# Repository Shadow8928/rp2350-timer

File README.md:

# XIAO-RP2350-Timer
I made this project in order to track the time i spend when doing certain tasks but i didn't want to use my phone in order to avoid distraction as well as when i study or work during the school day when i don't have my phone on me. originally the plan was to use an rp2040 chip with components but it proved too complicated for me to use and required equipment i didn't have. I decided on a xiao rp2350 as it already had lipo battery use prebuilt and was small to allow for the small form factor i was aiming for. 
## Parts List

| Item | Price | Link|
|---|---:|---|
| XIAO RP2350 | $1.09 | [AliExpress](https://www.aliexpress.us/item/3256812349541468.html) |
| Diodes | $2.49 | [AliExpress](https://www.aliexpress.us/item/3256807166031523.html) |
| LiPo battery | $1.09 | [AliExpress](https://www.aliexpress.us/item/3256803193874231.html) |
| Cherry switches | $0.33 | AliExpress — 3 for $0.99 |
| Buzzers | $0.33 | AliExpress — 3 for $0.99 |
| 0.91-inch OLED screen | $0.33 | AliExpress — 3 for $0.99 |
| LED diodes | $3.41 | [AliExpress](https://www.aliexpress.us/item/3256810339576661.html) |
| PCB | $11.01 | [JLCPCB](https://jlcpcb.com/) |
| Liquid flux | $4.85 | [AliExpress](https://www.aliexpress.us/item/3256804676815166.html) |
| **Total** | **$24.93** | |

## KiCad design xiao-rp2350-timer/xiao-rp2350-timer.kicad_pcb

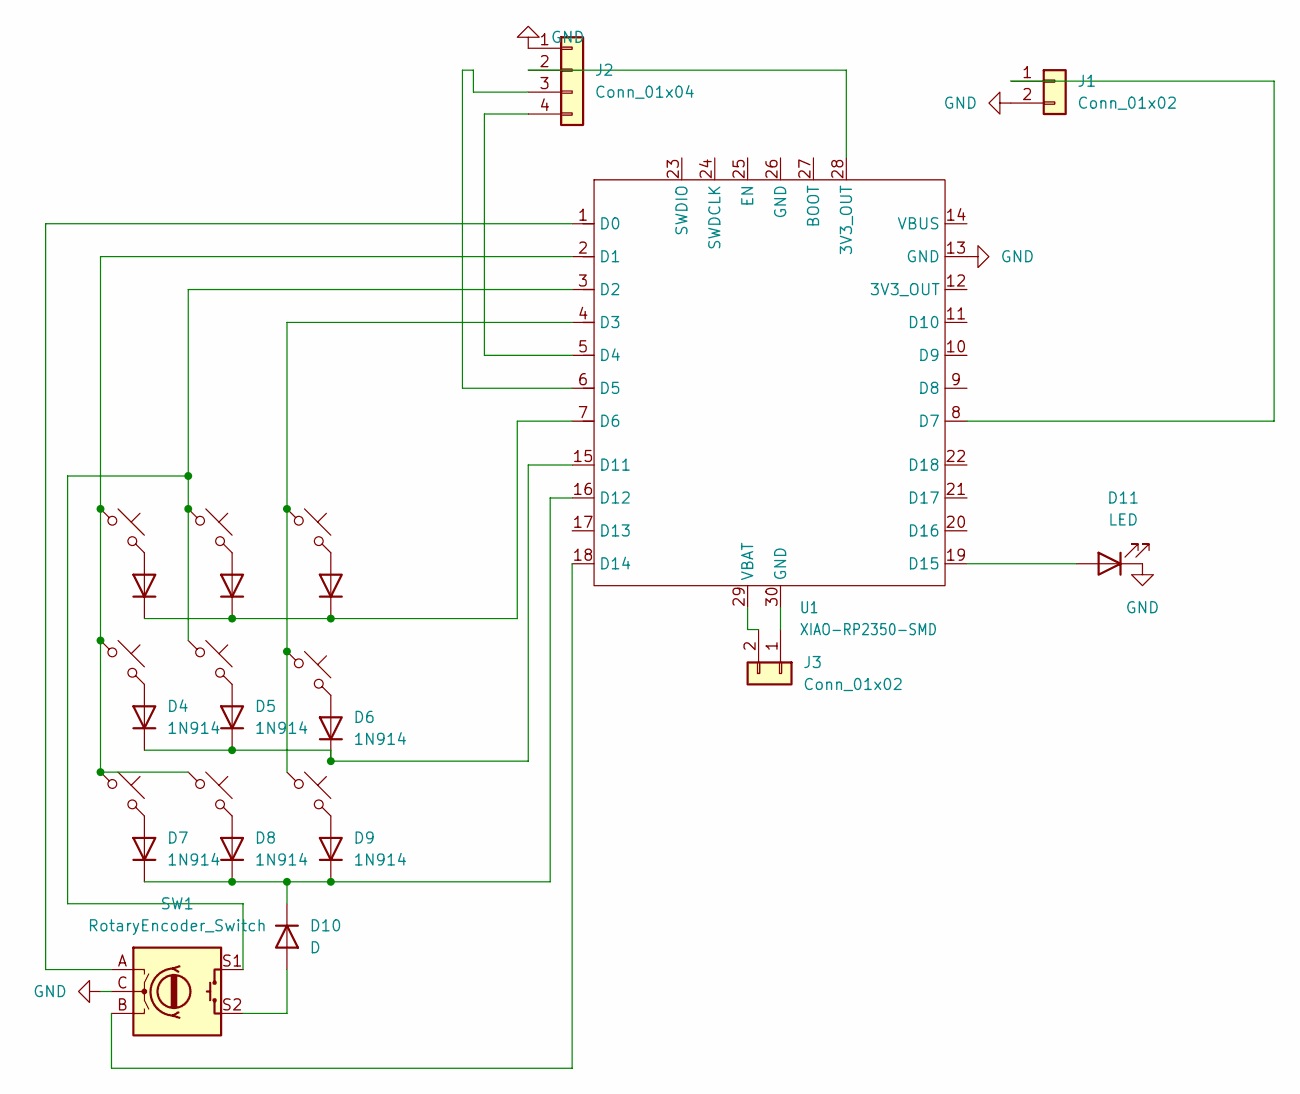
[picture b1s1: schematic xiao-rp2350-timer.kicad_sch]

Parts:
D1, D2, D3, D4, D5, D6, D7, D8, D9: 1N914; D_SOD-323_HandSoldering
D10: D; D_SOD-323_HandSoldering
D11: LED; LED_0805_2012Metric
J1, J3: Conn_01x02; JWT_A3963_1x02_P3.96mm_Vertical
J2: Conn_01x04; SSD1306-0.91-OLED-4pin-128x32
SW1: RotaryEncoder_Switch; RotaryEncoder_Alps_EC11E-Switch_Vertical_H20mm_MountingHoles
SW2, SW3, SW4, SW5, SW6, SW7, SW8, SW9, SW10: SW_Push_45deg; MX-Solderable-1U
U1: XIAO-RP2350-SMD

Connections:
GND: D11.1 (K), J1.2, J2.1, SW1.C, U1.13 (GND)
unnamed: D1.2 (A), SW2.2
unnamed: D1.1 (K), D2.1 (K), D3.1 (K), U1.7 (D6)
unnamed: D2.2 (A), SW3.2
unnamed: D3.2 (A), SW4.2
unnamed: D4.2 (A), SW5.2
unnamed: D4.1 (K), D5.1 (K), D6.1 (K), U1.15 (D11)
unnamed: D5.2 (A), SW6.2
unnamed: D6.2 (A), SW7.2
unnamed: D7.2 (A), SW8.2
unnamed: D8.2 (A), SW9.2
unnamed: D9.2 (A), SW10.2
unnamed: D10.2 (A), SW1.S2
unnamed: D7.1 (K), D8.1 (K), D9.1 (K), D10.1 (K), U1.16 (D12)
unnamed: D11.2 (A), U1.19 (D15)
unnamed: J1.1, U1.8 (D7)
unnamed: J2.2, U1.28 (3V3_OUT)
unnamed: J2.3, U1.6 (D5)
unnamed: J2.4, U1.5 (D4)
unnamed: J3.1, U1.30 (GND)
unnamed: J3.2, U1.29 (VBAT)
unnamed: SW1.A, U1.1 (D0)
unnamed: SW2.1, SW5.1, SW8.1, SW9.1, U1.2 (D1)
unnamed: SW1.S1, SW3.1, SW6.1, U1.3 (D2)
unnamed: SW4.1, SW7.1, SW10.1, U1.4 (D3)
unnamed: SW1.B, U1.18 (D14)

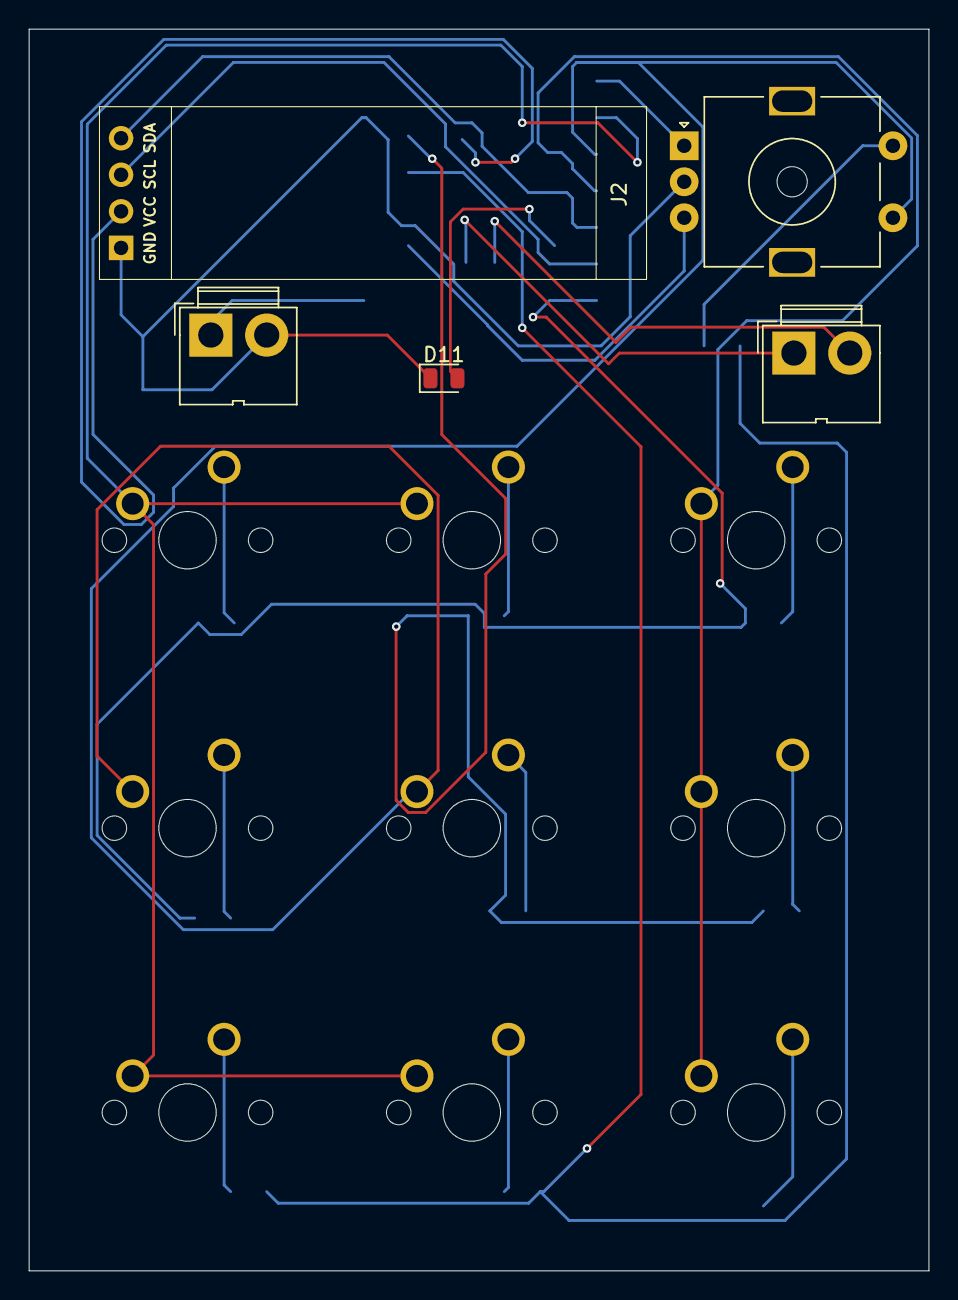
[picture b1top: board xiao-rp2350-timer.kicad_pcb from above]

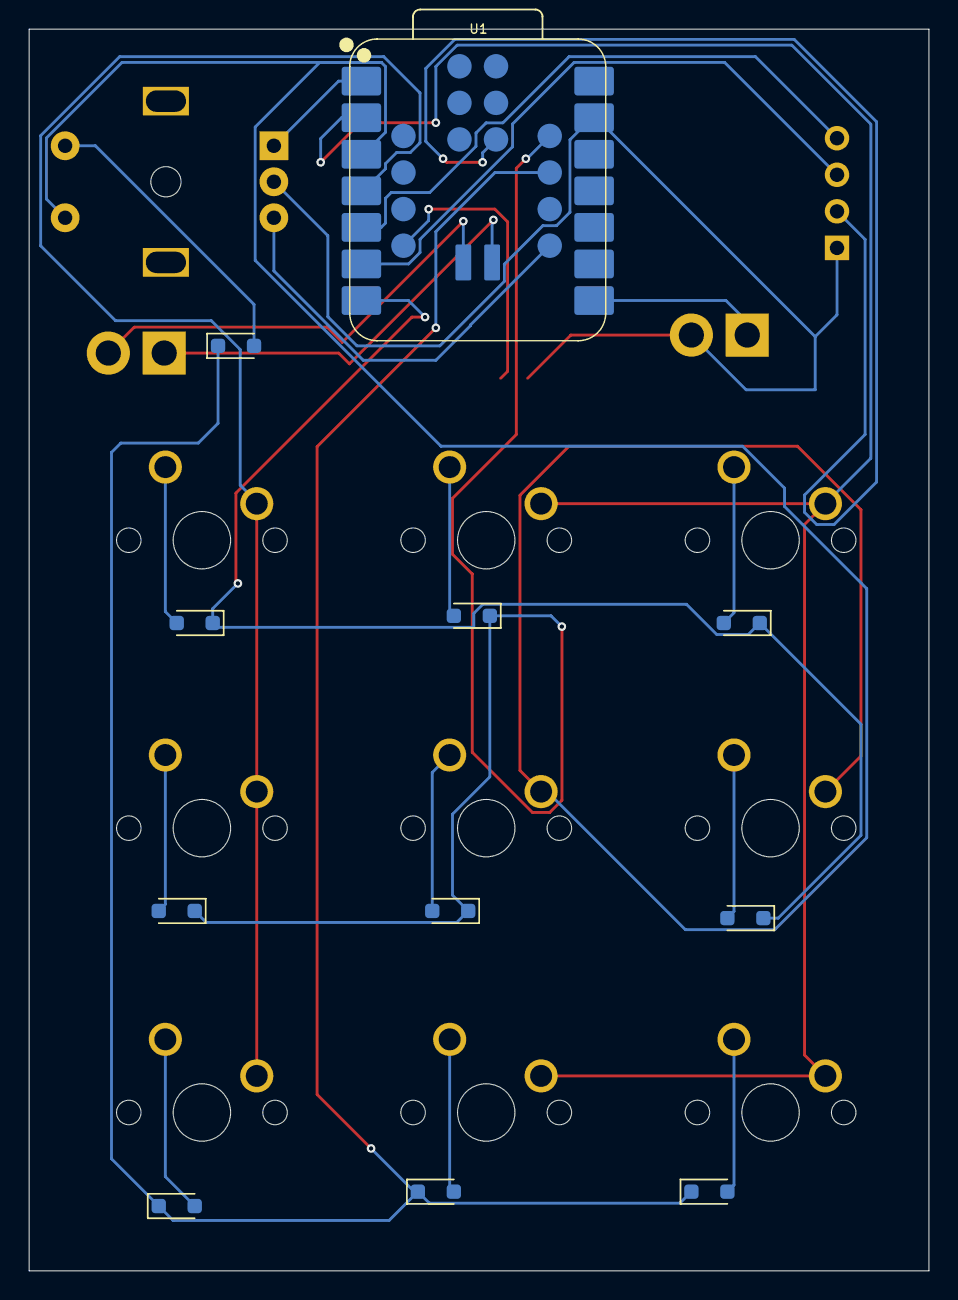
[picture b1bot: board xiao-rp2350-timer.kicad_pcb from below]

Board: 2 copper layers, 62.5 x 86.2 mm, 25 parts (11 on the bottom side), 26 nets.
